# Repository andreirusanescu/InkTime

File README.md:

# InkTime

An affordable, open-source smartwatch powered by the nRF52840 with an e-paper display, designed for low power consumption and BLE connectivity.

## Hardware Diagram

The InkTime smartwatch is built around the Nordic nRF52840 microcontroller and features the following subsystems:

```
                                    ┌───────────────────┐
                                    │    USB-C (J4)     │
                                    └──┬─────────────┬──┘
                                 VBUS  │             │ D+, D-
                                       │      ┌──────▼────────┐
                          ┌────────────┤      │  USBLC6 (D3)  │
                          │            │      │ ESD Protection│
                          │            │      └──────┬────────┘
                          │            │             │ D+, D- (protected)
                   ┌──────▼────────┐   │      ┌──────▼─────────────────────────┐
                   │  BQ25180 (IC3)│   │      │                                │
                   │  LiPo Charger │   │      │        nRF52840 (NRF52840_QF)  │
                   │  (I2C config) │   │      │        ARM Cortex-M4F @ 64MHz  │
                   └──────┬────────┘   │      │        BLE 5.0                 │
                          │            │      │                                │
                    VBAT  │     VBUS   │      │  ┌─────────────────────────┐   │
          ┌───────────────┤◄───────────┘      │  │ Interfaces:             │   │
          │               │                   │  │  SPI  → E-Paper Display │   │
   ┌──────▼────────┐      │                   │  │  I2C  → BMA423, DRV2605 │   │
   │ LiPo Battery  │      │                   │  │         MAX17048,       │   │
   │ LP502030      │      │                   │  │         BQ25180, RT6160 │   │
   │ 3.7V / 250mAh │      │                   │  │  USB  → USB-C (J4)      │   │
   └──────┬────────┘      │                   │  │  GPIO → Buttons, EPD    │   │
          │ VBAT          │                   │  │         ctrl, Haptic EN │   │
   ┌──────▼────────┐      │                   │  │  SWD  → TC2030 (J1)     │   │
   │ MAX17048 (U1) │──────│── I2C ───────────►│  └─────────────────────────┘   │
   │ Fuel Gauge    │      │                   │                                │
   │ (ALERT → GPIO)│      │                   │◄──── 32MHz Crystal (X1)        │
   └───────────────┘      │                   │◄──── 32.768kHz Crystal (X2)    │
                          │                   │◄──── 2.4GHz Antenna (ANT1)     │
                   ┌──────▼────────┐          │      via matching network      │
                   │  RT6160 (IC1) │          │      (L1, C3, C4, C9)          │
                   │  DC/DC        │          │                                │
                   │  Buck-Boost   │ VREG/3V3 │                                │
                   │  (I2C config) ├─────────►│                                │
                   └───────────────┘          └──┬──────┬──────┬───────────┬───┘
                                                 │      │      │           │
                              SPI (MOSI,SCK,CS)  │      │      │           │ GPIO
                              + GPIO ctrl        │      │ I2C  │ I2C       │ (SW_UP P0.26)
                                                 │      │      │           │ (SW_DN P0.27)
                  ┌──────────────────────┐       │      │      │       ┌───▼──────────────────┐
                  │  1.54" E-Paper (J2)  │◄──────┘      │      │       │  3×  │        Buttons│
                  │  200×200px SPI       │              │      │       │  EVP-AKE31A          │
                  │                      │              │      │       │  (SW_ENT P1.00)      │
                  │  EPD Boost Circuit:  │              │      │       └──────────────────────┘
                  │  Q1 (DMG2305UX)      │              │      │
                  │  Q3 (SI1308EDL)      │       ┌──────▼──┐   │
                  │  D2,D4,D5 (MBR0530)  │       │ BMA423  │   │
                  │  L5 (68µH)           │       │  (IC2)  │   │
                  │  → PREVGH, PREVGL    │       │  IMU    │   │
                  └──────────────────────┘       └─────────┘   │
                                                        ┌──────▼──────┐
                           ┌──────────────┐             │  DRV2605    │
                           │  TC2030 (J1) │             │   (IC4)     │
                           │  SWD Debug   │             │  Haptic     │
                           │  (SWDIO,     │             │  Driver     │
                           │   SWDCLK,    │             │  + Motor    │
                           │   SWO, RST)  │             │  (FIT0774)  │
                           └──────────────┘             └─────────────┘
```

## Bill of Materials (BOM)

| Component | Value/Part Number | Package | Qty | Description | Datasheet |
|-----------|-------------------|---------|-----|-------------|-----------|
| NRF52840_QF | nRF52840 | AQFN-73 | 1 | MCU with BLE 5.0 | [Datasheet](https://infocenter.nordicsemi.com/pdf/nRF52840_PS_v1.1.pdf) |
| IC1 | RT6160AWSC | WL-CSP-15 | 1 | DC/DC Buck-Boost Converter | [Datasheet](https://www.richtek.com/assets/product_file/RT6160A/DS6160A-05.pdf) |
| IC2 | BMA423 | LGA-12 | 1 | Triaxial Accelerometer (IMU) | [Datasheet](https://www.bosch-sensortec.com/products/motion-sensors/accelerometers/bma423/) |
| IC3 | BQ25180YBGR | DSBGA-8 | 1 | LiPo Charger | [Datasheet](https://www.ti.com/lit/ds/symlink/bq25180.pdf) |
| IC4 | DRV2605YZFR | WCSP-9 | 1 | Haptic Driver | [Datasheet](https://www.ti.com/lit/ds/symlink/drv2605.pdf) |
| U1 | MAX17048G+T10 | TDFN-8 | 1 | Fuel Gauge | [Datasheet](https://www.analog.com/media/en/technical-documentation/data-sheets/max17048-max17049.pdf) |
| D3 | USBLC6-2SC6Y | SOT-23-6 | 1 | ESD Protection | [Datasheet](https://www.st.com/resource/en/datasheet/usblc6-2.pdf) |
| ANT1 | 2450AT18B100E | SMD | 1 | 2.4GHz Chip Antenna | [Datasheet](https://www.johansontechnology.com/datasheets/antennas/2450AT18B100.pdf) |
| X1 | 32MHz Crystal | SMD 2016 | 1 | Main Clock | - |
| X2 | 32.768kHz Crystal | SMD 3215 | 1 | RTC Clock | - |
| J1 | TC2030-IDC | Tag-Connect | 1 | SWD Debug Header | [Datasheet](https://www.tag-connect.com/product/tc2030-idc) |
| J2 | 503480-2400 | FPC-24 | 1 | E-Paper FPC Connector | [Datasheet](https://www.molex.com/en-us/part-list/503480-2400) |
| J4 | KH-TYPE-C-16P | SMD | 1 | USB-C Connector | - |
| Q1 | DMG2305UX-7 | SOT-23 | 1 | P-Ch MOSFET (EPD drive) | [Datasheet](https://www.diodes.com/assets/Datasheets/DMG2305UX.pdf) |
| Q3 | SI1308EDL-T1-GE3 | SC-70 | 1 | N-Ch MOSFET (EPD drive) | [Datasheet](https://www.vishay.com/docs/68986/si1308edl.pdf) |
| D2, D4, D5 | MBR0530 | SOD-123 | 3 | Schottky Diode (EPD drive) | - |
| L1 | 3.9nH | SMD 2012 | 1 | RF Matching Network | - |
| L2 | 10µH | SMD 2012 | 1 | nRF Power Inductor | - |
| L3 | 15nH | SMD 2012 | 1 | RF Filter | - |
| L5 | 68µH | SMD 2012 | 1 | EPD Boost Inductor | - |
| L7 | FTC252012SR47MBCA | SMD 2012 | 1 | DC/DC Power Inductor (0.47µH) | [JLCPCB](https://jlcpcb.com/partdetail/6763488-FTC252012SR47MBCA/C5832368) |
| SW_UP, SW_DN, SW_ENT | EVP-AKE31A | SMD | 3 | Tactile Buttons | - |
| SJ1 | Solder Jumper | SMD | 1 | Configuration Jumper | - |
| R1, R2, R5 | 0Ω | 0201 | 3 | Zero-ohm Resistors | - |
| R3, R4 | 3.3kΩ | 0201 | 2 | I2C Pull-up Resistors | - |
| R6, R2_EP_DR, R_PWR_EPD | 10kΩ | 0201 | 3 | Pull-up/Pull-down | - |
| R7, R8, R9 | 10kΩ | 0201 | 3 | Button Pull-down Resistors | - |
| R1_USB, R2_USB | 5.1kΩ | 0201 | 2 | USB-C CC Pull-down | - |
| R_TYPE_SEL | 2.2Ω | 0201 | 1 | EPD Type Select | - |
| R1_EP_DR | 0.47Ω | 0201 | 1 | EPD Current Sense | - |
| C1, C2, C17, C18 | 12pF | 0201 | 4 | Crystal Load Capacitors | - |
| C3, C4 | 1pF | 0201 | 2 | RF Matching | - |
| C9 | 820pF | 0201 | 1 | RF Matching | - |
| C5, C7, C8, C12, C19 | 100nF | 0201 | 5 | Decoupling Capacitors | - |
| C11 | 100pF | 0201 | 1 | Decoupling (DEC5) | - |
| C16 | 47nF | 0201 | 1 | Decoupling | - |
| C15 | 1.0µF | 0402 | 1 | Decoupling | - |
| C6, C14, C20, C21, C43, C2-EP-DR | 4.7µF | 0402 | 6 | Bulk Capacitors | - |
| C24, C39, C1-EP-DR | 10µF | 0402 | 3 | Input/Output Caps | - |
| C25, C33 | 22µF | 0402 | 2 | DC/DC Output Caps | - |
| C23, C27, C34, C42, EPD_C5 | 0.1µF | 0201 | 5 | Decoupling | - |
| C29-C32, C37, C38, EPD_C1-C12 | 1µF | 0402 | 15 | Filter/Bypass Caps | - |
| C10, C13, C22 | N.C. | 0201 | 3 | Do Not Populate | - |
| Test Pads | - | SMD | 14 | TP_GND, TP_3V3, TP_VBAT, etc. | - |

## Hardware Description

### Microcontroller — nRF52840 (NRF52840_QF)
The nRF52840 is the core of the InkTime, providing Bluetooth Low Energy 5.0 connectivity, ARM Cortex-M4F processing at 64MHz, and extensive GPIO. It communicates with peripherals via I2C and SPI buses and is powered by 3.3V from the RT6160 DC/DC converter.

Two crystals provide clock sources: a 32MHz crystal (X1) connected to XC1/XC2 with 12pF load capacitors (C1, C2), and a 32.768kHz crystal (X2) connected to P0.00/XL1 and P0.01/XL2 with 12pF load capacitors (C17, C18).

The RF section uses a 2450AT18B100E chip antenna connected through an impedance matching network (L1=3.9nH, C3=1pF, C4=1pF, C9=820pF) to the ANT pin. The antenna is placed at the edge of the PCB with a copper keepout zone on all layers underneath.

Decoupling capacitors placed close to corresponding power pins: C5 (100nF) on DEC1, C8 (100nF) on DEC3, C7 (100nF) on DEC4_6, C11 (100pF) on DEC5, C15 (1.0µF). Capacitors C10, C13, C22 are N.C. (Do Not Populate) per Nordic's reference design.

### Power Management

**LiPo Charger — BQ25180 (IC3):** Manages battery charging from USB-C (VBUS). Single-cell LiPo battery connected directly to test pads (TP_VBAT, TP_BAT_GND). I2C configurable. Interrupt output (PMIC_INT) to nRF52840. Bypass capacitors C37 (1µF), C39 (10µF). Pull-up R6 (10kΩ) on TS/MR.

**DC/DC Converter — RT6160 (IC1):** Buck-boost converter, VBAT (3.0–4.2V) to VREG/3V3. I2C voltage selection via VSEL pin. Power inductor L7 (0.47µH). Input cap C23 (0.1µF), output caps C24 (10µF), C25 (22µF), C33 (22µF). I2C pull-ups R3, R4 (3.3kΩ).

**Fuel Gauge — MAX17048 (U1):** Battery monitoring via I2C. CELL pin to VBAT, ALERT output to nRF52840. Bypass cap C38 (1µF).

### Display — 1.54" E-Paper (via J2, 503480-2400)
SPI interface (MOSI, SCK, EPD_CS). Drive circuit with Q3 (SI1308EDL), Q1 (DMG2305UX), diodes D2/D4/D5 (MBR0530), inductor L5 (68µH), and capacitors EPD_C1–C12 for high-voltage generation (PREVGH, PREVGL). Control: EPD_RST, EPD_BUSY, EPD_DC.

### IMU — BMA423 (IC2)
Triaxial accelerometer via I2C (SDA, SCL). Two interrupt outputs (IMU_INT1, IMU_INT2) for motion/step/gesture detection. Decoupling C19 (100nF). Zero-ohm resistors R1, R2, R5 for pin configuration.

### Haptic Driver — DRV2605 (IC4)
I2C haptic driver for vibration motor (FIT0774). Enable via HAPTIC_EN GPIO. Decoupling C32 (1µF), C34 (0.1µF).

### USB-C and ESD Protection
KH-TYPE-C-16P connector (J4). USBLC6-2SC6Y (D3) ESD protection. CC pull-downs R1_USB, R2_USB (5.1kΩ). Bypass caps C42 (0.1µF), C43 (4.7µF).

### SWD Debug — TC2030-IDC (J1)
Tag-Connect pogo-pin interface: SWDIO, SWDCLK, SWO, RESET, 3.3V, GND. No permanent connector needed.

## nRF52840 Pin Assignment

| Pin | Signal | Function | Interface |
|-----|--------|----------|-----------|
| P0.00/XL1 | XL1 | 32.768kHz Crystal | Clock |
| P0.01/XL2 | XL2 | 32.768kHz Crystal | Clock |
| P0.04/AIN2 | IMU_INT1 | BMA423 Interrupt 1 | GPIO |
| P0.05/AIN3 | IMU_INT2 | BMA423 Interrupt 2 | GPIO |
| P0.06 | EPD_CS | E-Paper Chip Select | SPI |
| P0.07 | EPD_DC | E-Paper Data/Command | GPIO |
| P0.08 | EPD_RST | E-Paper Reset | GPIO |
| P0.09/NFC1 | PMIC_INT | BQ25180 Interrupt | GPIO |
| P0.11 | SCK | SPI Clock (E-Paper) | SPI |
| P0.12 | MOSI | SPI Data (E-Paper) | SPI |
| P0.13 | EPD_BUSY | E-Paper Busy | GPIO |
| P0.14 | SCL | I2C Clock | I2C |
| P0.15 | SDA | I2C Data | I2C |
| P0.18/RESET | RESET | System Reset | Reset |
| P0.19 | HAPTIC_EN | DRV2605 Enable | GPIO |
| P0.26 | SW_UP | Button Up | GPIO |
| P0.27 | SW_DN | Button Down | GPIO |
| P1.00 | SW_ENT | Button Enter | GPIO |
| P1.01 | ALERT | MAX17048 Alert | GPIO |
| P1.09 | SWO | Debug Trace Output | Debug |
| XC1/XC2 | Crystal | 32MHz Oscillator | Clock |
| ANT | RF | Antenna via matching | RF |
| VBUS | USB_VBUS | USB Power (5V) | Power |
| D+/D- | USB Data | USB Data Lines | USB |
| SWDIO | Debug | SWD Data | Debug |
| SWDCLK | Debug | SWD Clock | Debug |

**I2C Bus** shared by: BMA423 (IC2), BQ25180 (IC3), RT6160 (IC1), DRV2605 (IC4), MAX17048 (U1). Pull-ups R3, R4 (3.3kΩ) to 3V3.

## PCB Design Details

### Board Specifications
- **Dimensions:** 46mm × 35mm, rounded corners
- **Layers:** 4 (Top, Route2, Route63, Bottom)
- **Thickness:** 1.0mm
- **Trace widths:** 0.15mm (signals), 0.3mm (power)
- **Components:** All on TOP layer

### Layer Stack
| Layer | Name | Function |
|-------|------|----------|
| 1 | ct Top | Signals + GND polygon |
| 2 | c2 Route2 | Dedicated GND plane |
| 63 | c63 Route63 | Signal routing |
| 64 | cb Bottom | Signals + GND polygon |

### Design Decisions and Accepted Errors
- **Copper Width errors (accepted)**: Power nets (3V3, VREG, VBAT, VBUS, etc.) require 0.3mm trace width per design rules. However, in some dense areas of the board - particularly around small IC packages and tight pad spacing - there is not enough physical space to maintain 0.3mm width for the entire trace length. The resulting DRC errors were accepted.
- **Copper Clearance errors (accepted)**: In highly congested areas, especially around the nRF52840 BGA and the dense passive component clusters, some traces and pads come closer together than the 0.15mm clearance rule allows. These violations occur where component placement leaves no alternative routing path and were accepted after manual verification that no actual shorts exist.
- **Overlapping / Polygon Clearance errors (accepted)**: Some GND polygons on different layers generate clearance warnings where they overlap with same-rank polygons. These are non-functional warnings — the polygons are all on the same net (GND) and do not cause electrical issues.
- **Board Outline Clearance errors (accepted)**: The three tactile buttons (SW_UP, SW_DN, SW_ENT) and the USB-C connector (J4) intentionally extend beyond the PCB edge for mechanical alignment with the enclosure cutouts. This is by design and explicitly permitted in the project specification.
- **N.C. capacitors (C10, C13, C22):** Footprints present but not populated per Nordic reference.
- **Silkscreen:** Labels on IC's, connectors, test pads, capacitors etc.
- **Via stitching**: GND vias are distributed across the board between all ground planes, with higher concentration around the nRF52840 and RF antenna area, to ensure low-impedance ground return paths at 2.4GHz.

## Mechanical

| Component | Dimensions | Notes |
|-----------|-----------|-------|
| Battery (AKYGA LP502030) | 32.5 × 21 × 5.5mm | 3.7V/250mAh, soldered to test pads |
| Display (1.54" e-Paper V2) | 37.32 × 31.80 × 1.05mm | 200×200px, SPI, ultra-low power |
| Vibration Motor (FIT0774) | Ø10 × 2.7mm | 1.5–4.2VDC, 50mA |
| Enclosure | Custom | 3D-printed, cutouts for USB/buttons |

## Repository Structure

```
├── Hardware/
│   ├── InkTime_Schematic.sch
│   └── InkTime_Board.brd
├── Manufacturing/
│   ├── gerbers.zip
│   ├── InkTime_BOM.bom
│   └── InkTime_PnP.cpl
├── Mechanical/
│   ├── InkTime_step.step
│   └── InkTime_complete.f3z
├── Images/
│   ├── 2D_PCB/          (PCB layer views: Top, Bottom, C2, C63)
│   ├── 3D_PCB/          (3D renders of the PCB)
│   ├── InkTime/         (Watch assembly renders)
│   └── Schematic/       (Schematic screenshots)
├── LICENSE
└── README.md
```

## Images

### Watch Assembly

| Top View | Side View (Buttons) | USB-C Port |
|----------|---------------------|------------|
|  |  |  |

### Exploded View

| Side View (Exploded) | Front View (Exploded) |
|----------------------|-----------------------|
|  |  |

### 3D Component Models

| Display (Top) | Display (Side — Rounded Edges) | Display (Edges) |
|---------------|-------------------------------|-----------------|
|  |  |  |

| Battery (LP502030) | Shaker Motor (FIT0774) |
|--------------------|------------------------|
|  |  |

### PCB Renders

| 3D Top View | 3D Side View |
|-------------|--------------|
|  |  |

### PCB Layers

| Top Layer | Inner Layer 2 (GND) | Inner Layer 63 (Signal) | Bottom Layer |
|-----------|---------------------|------------------------|--------------|
|  |  |  |  |

### Schematic

| Page 1 | Page 2 |
|--------|--------|
|  |  |

## License

This project is open source hardware, licensed under the [Apache License 2.0](LICENSE).

Distributed as-is; no warranty is given.

---

*Designed as part of the InkTime project — TSC course, Politehnica Bucharest, 2026.*

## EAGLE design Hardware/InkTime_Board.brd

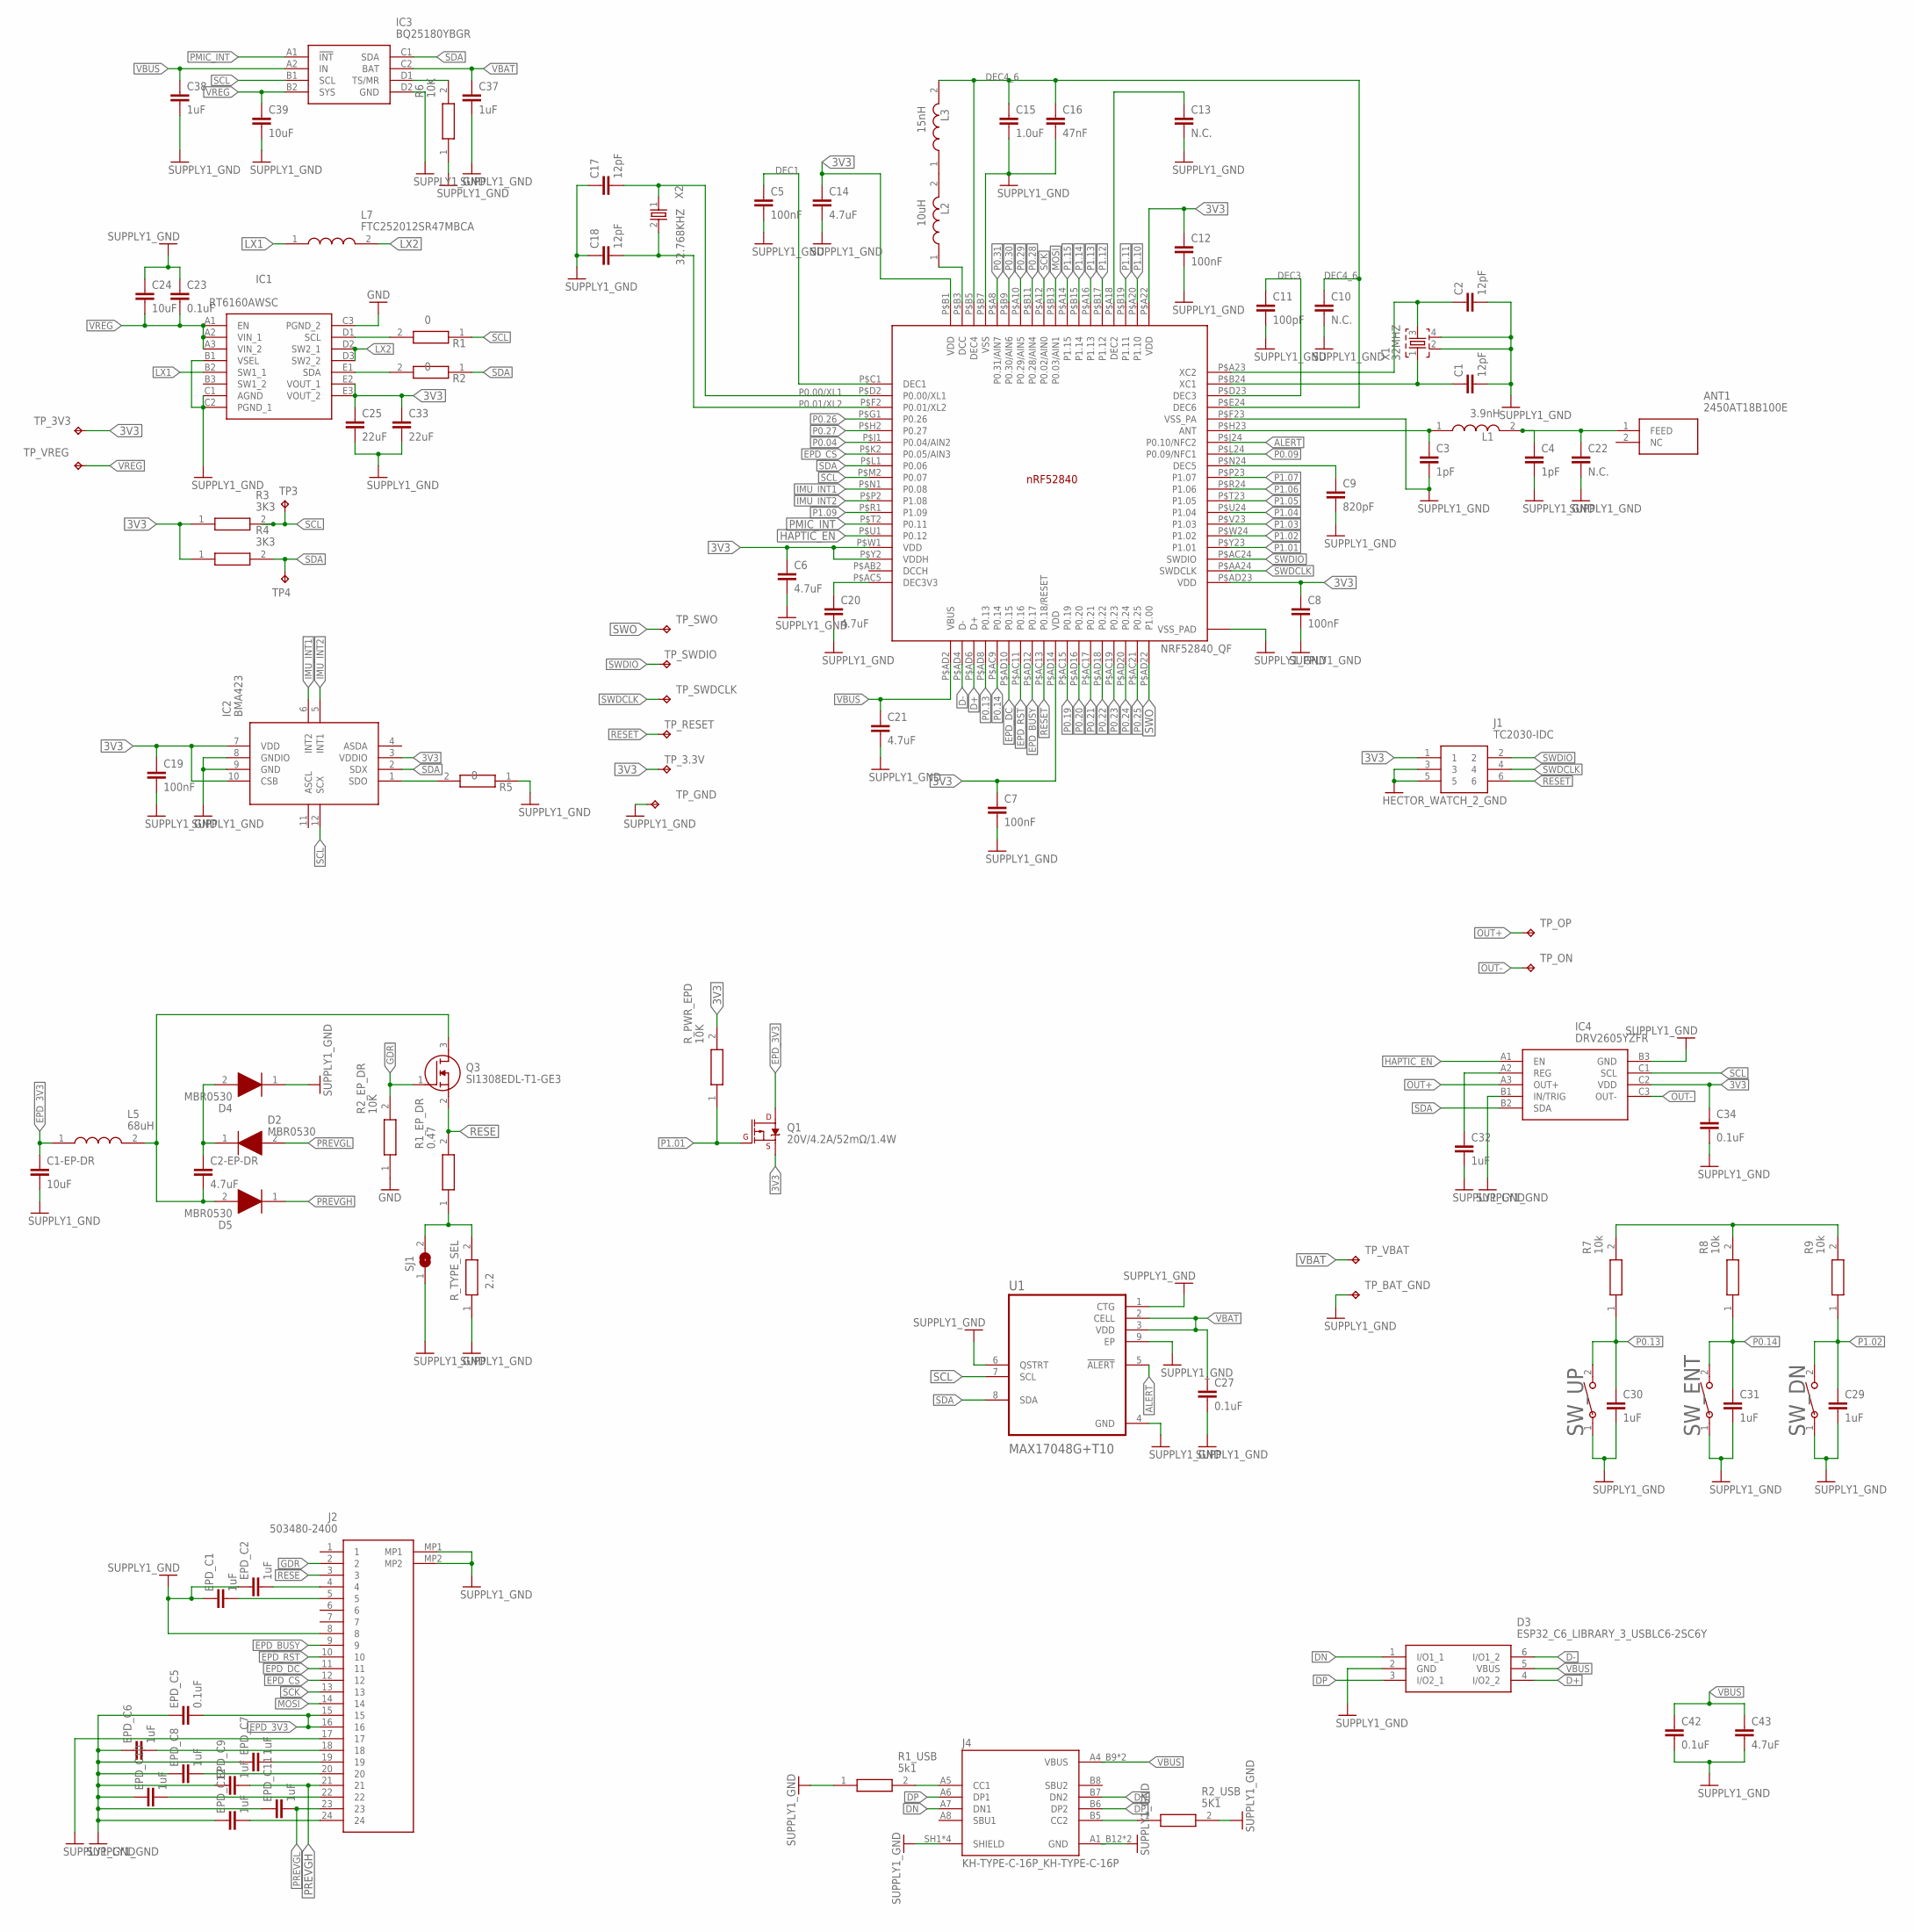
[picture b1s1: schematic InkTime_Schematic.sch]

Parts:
ANT1: 2450AT18B100E; 2450AT18B100E_ANTC3216X140N
C1, C2, C17, C18: 12pF; NORDIC_NRF_3_RESC0201_L
C1-EP-DR, C24, C39: 10uF; NORDIC_NRF_3_RESC0402_L
C2-EP-DR, C6, C14, C20, C21, C43: 4.7uF; NORDIC_NRF_3_RESC0402_L
C3, C4: 1pF; NORDIC_NRF_3_RESC0201_L
C5, C7, C8, C12, C19: 100nF; NORDIC_NRF_3_RESC0201_L
C9: 820pF; NORDIC_NRF_3_RESC0201_L
C10, C13, C22: N.C.; NORDIC_NRF_3_RESC0201_L
C11: 100pF; NORDIC_NRF_3_RESC0201_L
C15: 1.0uF; NORDIC_NRF_3_RESC0402_L
C16: 47nF; NORDIC_NRF_3_RESC0201_L
C23, C27, C34, C42: 0.1uF; NORDIC_NRF_3_RESC0201_L
C25, C33: 22uF; NORDIC_NRF_3_RESC0402_L
C29, C30, C31, C32, C37, C38: 1uF; NORDIC_NRF_3_RESC0402_L
D2, D4, D5: MBR0530; ESP32_C6_LIBRARY_5_SOD3716X135N
D3: ESP32_C6_LIBRARY_3_USBLC6-2SC6Y; ESP32_C6_LIBRARY_3_SOT95P280X145-6N
EPD_C1, EPD_C2, EPD_C6, EPD_C7, EPD_C8, EPD_C9, EPD_C10, EPD_C11, EPD_C12: 1uF; NORDIC_NRF_3_RESC0402_L
EPD_C5: 0.1uF; NORDIC_NRF_3_RESC0201_L
IC1: RT6160AWSC; RT6160AWSC_BGA15C40P3X5_140X230X60
IC2: BMA423; BMA423_BMA423
IC3: BQ25180YBGR; BQ25180YBGR_BGA8C40P2X4_100X155X50
IC4: DRV2605YZFR; DRV2605YZFR_BGA9C50P3X3_144X144X62
J1: TC2030-IDC; TC2030-IDC_TC2030IDC
J2: 503480-2400; 503480-2400_5034802400
J4: KH-TYPE-C-16P_KH-TYPE-C-16P; KH-TYPE-C-16P_KINGHELM_KH-TYPE-C-16P
L1: 3.9nH; MLP2016SR47MT0S1_INDC2016X100N
L2: 10uH; MLP2016SR47MT0S1_INDC2016X100N
L3: 15nH; MLP2016SR47MT0S1_INDC2016X100N
L5: 68uH; MLP2016SR47MT0S1_INDC2016X100N
L7: FTC252012SR47MBCA; MLP2016SR47MT0S1_INDC2016X100N
NRF52840_QF: NRF52840_QF; NORDIC_NRF_4_AQFN50P700X700X85_HS-74N
Q1: 20V/4.2A/52mΩ/1.4W; ESP32_C6_LIBRARY_4_ESP32_C6_LIBRARY_4_ESP32_C6_LIBRARY_4_ES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
Q3: SI1308EDL-T1-GE3; ESP32_C6_LIBRARY_6_SOT65P210X110-3N
R1, R2, R5: 0; CPF0201D7K68C1_0201
R1_EP_DR: 0.47; CPF0201D7K68C1_0201
R1_USB: 5k1; CPF0201D7K68C1_0201
R2_EP_DR, R6: 10K; CPF0201D7K68C1_0201
R2_USB: 5K1; CPF0201D7K68C1_0201
R3, R4: 3K3; CPF0201D7K68C1_0201
R7, R8, R9: 10k; CPF0201D7K68C1_0201
R_PWR_EPD: 10K; CPF0201D7K68C1_0201
R_TYPE_SEL: 2.2; CPF0201D7K68C1_0201
SJ1: ESP32_C6_LIBRARY_7_JUMPER_SJ
SW_DN: EVP-AKE31A_PAN; 2025-10-22_07-23-44_LIBRARY_SW_EVP-AKE31A_PAN
SW_ENT: EVP-AKE31A_PAN; 2025-10-22_07-23-44_LIBRARY_SW_EVP-AKE31A_PAN
SW_UP: EVP-AKE31A_PAN; 2025-10-22_07-23-44_LIBRARY_SW_EVP-AKE31A_PAN
TP3, TP4: HECTOR_WATCH_1_TPTP20R; HECTOR_WATCH_1_TP20R
TP_3.3V, TP_3V3: HECTOR_WATCH_1_TPTP20R; HECTOR_WATCH_1_TP20R
TP_BAT_GND: HECTOR_WATCH_1_TPTP20R; HECTOR_WATCH_1_TP20R
TP_GND: HECTOR_WATCH_1_TPTP20R; HECTOR_WATCH_1_TP20R
TP_ON: HECTOR_WATCH_1_TPTP20R; HECTOR_WATCH_1_TP20R
TP_OP: HECTOR_WATCH_1_TPTP20R; HECTOR_WATCH_1_TP20R
TP_RESET: HECTOR_WATCH_1_TPTP20R; HECTOR_WATCH_1_TP20R
TP_SWDCLK: HECTOR_WATCH_1_TPTP20R; HECTOR_WATCH_1_TP20R
TP_SWDIO: HECTOR_WATCH_1_TPTP20R; HECTOR_WATCH_1_TP20R
TP_SWO: HECTOR_WATCH_1_TPTP20R; HECTOR_WATCH_1_TP20R
TP_VBAT: HECTOR_WATCH_1_TPTP20R; HECTOR_WATCH_1_TP20R
TP_VREG: HECTOR_WATCH_1_TPTP20R; HECTOR_WATCH_1_TP20R
U1: MAX17048G+T10; ESP32_C6_LIBRARY_SON50P200X200X80-9N
X1: 32MHZ; NORDIC_NRF_BT-XTAL_2016_N
X2: 32.768KHZ; NORDIC_NRF_1_XTAL_3215_N

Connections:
3V3: C7.1, C8.1, C12.1, C14.1, C19.1, C34.1, IC2.3 (VDDIO), IC2.7 (VDD), IC2.10 (CSB), IC4.C2 (VDD), J1.1, NRF52840_QF.P$A22 (VDD), NRF52840_QF.P$AD14 (VDD), NRF52840_QF.P$AD23 (VDD), NRF52840_QF.P$B1 (VDD), Q1.2 (S), R_PWR_EPD.2, TP_3.3V.TP, TP_3V3.TP
ALERT: NRF52840_QF.P$J24 (P0.10/NFC2), U1.5 (!ALERT)
D+: D3.4 (I/O2_2), NRF52840_QF.P$AD6 (D+)
D-: D3.6 (I/O1_2), NRF52840_QF.P$AD4 (D-)
DEC1: C5.1, NRF52840_QF.P$C1 (DEC1)
DEC3: C11.1, NRF52840_QF.P$D23 (DEC3)
DEC4_6: C10.1, C15.1, C16.1, L3.2, NRF52840_QF.P$B5 (DEC4), NRF52840_QF.P$E24 (DEC6)
DN: D3.1 (I/O1_1), J4.A7 (DN1), J4.B7 (DN2)
DP: D3.3 (I/O2_1), J4.A6 (DP1), J4.B6 (DP2)
EPD_3V3: C1-EP-DR.1, EPD_C5.2, J2.15, J2.16, L5.1, Q1.3 (D)
EPD_BUSY: J2.9, NRF52840_QF.P$AD12 (P0.17)
EPD_CS: J2.12, NRF52840_QF.P$K2 (P0.05/AIN3)
EPD_DC: J2.11, NRF52840_QF.P$AD10 (P0.15)
EPD_RST: J2.10, NRF52840_QF.P$AC11 (P0.16)
GDR: J2.2, Q3.1 (G), R2_EP_DR.2
GND: C1.2, C1-EP-DR.2, C2.2, C3.2, C4.2, C5.2, C6.2, C7.2, C8.2, C9.2, C10.2, C11.2, C12.2, C13.2, C14.2, C15.2, C16.2, C17.1, C18.1, C19.2, C20.2, C21.2, C22.2, C23.1, C24.1, C25.2, C27.2, C29.2, C30.2, C31.2, C32.2, C33.2, C34.2, C37.2, C38.2, C39.2, C42.2, C43.2, D3.2 (GND), D4.1 (K), EPD_C1.1, EPD_C2.1, EPD_C5.1, EPD_C6.1, EPD_C7.1, EPD_C8.1, EPD_C9.1, EPD_C10.1, EPD_C11.1, EPD_C12.1, IC1.B1 (VSEL), IC1.C1 (AGND), IC1.C2 (PGND_1), IC1.C3 (PGND_2), IC2.8 (GNDIO), IC2.9 (GND), IC3.D2 (GND), IC4.B1 (IN/TRIG), IC4.B3 (GND), J1.3, J1.5, J2.8, J2.17, J2.MP1, J2.MP2, J4.A1_B12 (GND), J4.A12_B1 (GND), J4.SH1 (SHIELD), J4.SH2 (SHIELD), J4.SH3 (SHIELD), J4.SH4 (SHIELD), NRF52840_QF.P$74 (VSS_PAD), NRF52840_QF.P$75 (VSS_PAD), NRF52840_QF.P$76 (VSS_PAD), NRF52840_QF.P$77 (VSS_PAD), NRF52840_QF.P$78 (VSS_PAD), NRF52840_QF.P$79 (VSS_PAD), NRF52840_QF.P$80 (VSS_PAD), NRF52840_QF.P$81 (VSS_PAD), NRF52840_QF.P$82 (VSS_PAD), NRF52840_QF.P$83 (VSS_PAD), NRF52840_QF.P$84 (VSS_PAD), NRF52840_QF.P$85 (VSS_PAD), NRF52840_QF.P$86 (VSS_PAD), NRF52840_QF.P$87 (VSS_PAD), NRF52840_QF.P$88 (VSS_PAD), NRF52840_QF.P$89 (VSS_PAD), NRF52840_QF.P$90 (VSS_PAD), NRF52840_QF.P$B7 (VSS), NRF52840_QF.P$F23 (VSS_PA), R1_USB.1, R2_EP_DR.1, R2_USB.2, R5.1, R6.1, R_TYPE_SEL.1, SJ1.1, SW_DN.1, SW_ENT.1, SW_UP.1, TP_BAT_GND.TP, TP_GND.TP, U1.1 (CTG), U1.4 (GND), U1.6 (QSTRT), U1.9 (EP), X1.2, X1.4
HAPTIC_EN: IC4.A1 (EN), NRF52840_QF.P$U1 (P0.12)
IMU_INT1: IC2.6 (INT2), NRF52840_QF.P$N1 (P0.08)
IMU_INT2: IC2.5 (INT1), NRF52840_QF.P$P2 (P1.08)
LX1: IC1.B2 (SW1_1), L7.1
LX2: IC1.D2 (SW2_1), IC1.D3 (SW2_2), L7.2
MOSI: J2.14, NRF52840_QF.P$B13 (P0.03/AIN1)
unnamed: C1.1, NRF52840_QF.P$B24 (XC1), X1.1
unnamed: ANT1.1 (FEED), C4.1, C22.1, L1.2
unnamed: C3.1, L1.1, NRF52840_QF.P$H23 (ANT)
unnamed: C2.1, NRF52840_QF.P$A23 (XC2), X1.3
unnamed: C6.1, NRF52840_QF.P$W1 (VDD), NRF52840_QF.P$Y2 (VDDH)
unnamed: C20.1, NRF52840_QF.P$AC5 (DEC3V3)
unnamed: C13.1, NRF52840_QF.P$A18 (DEC2)
unnamed: L2.1, NRF52840_QF.P$B3 (DCC)
unnamed: L2.2, L3.1
unnamed: IC1.D1 (SCL), R1.2
unnamed: IC1.E1 (SDA), R2.2
unnamed: C9.1, NRF52840_QF.P$N24 (DEC5)
unnamed: C25.1, C33.1, IC1.E2 (VOUT_1), IC1.E3 (VOUT_2)
unnamed: R3.1, R4.1
unnamed: C2-EP-DR.1, D2.1 (K), D4.2 (A)
unnamed: IC2.1 (SDO), R5.2
unnamed: C2-EP-DR.2, D5.2 (A), L5.2, Q3.3 (D)
unnamed: IC3.D1 (TS/MR), R6.2
unnamed: R1_EP_DR.1, R_TYPE_SEL.2, SJ1.2
unnamed: C32.1, IC4.A2 (REG)
unnamed: R7.2, R8.2, R9.2
unnamed: J4.A5 (CC1), R1_USB.2
unnamed: EPD_C12.2, J2.24
unnamed: EPD_C2.2, J2.4
unnamed: EPD_C1.2, J2.5
unnamed: J4.B5 (CC2), R2_USB.1
unnamed: EPD_C6.2, J2.18
unnamed: EPD_C7.2, J2.19
unnamed: EPD_C8.2, J2.20
unnamed: EPD_C10.2, J2.22
OUT+: IC4.A3 (OUT+), TP_OP.TP
OUT-: IC4.C3 (OUT-), TP_ON.TP
P0.00/XL1: C17.2, NRF52840_QF.P$D2 (P0.00/XL1), X2.1
P0.01/XL2: C18.2, NRF52840_QF.P$F2 (P0.01/XL2), X2.2
P0.04: NRF52840_QF.P$J1 (P0.04/AIN2)
P0.09: NRF52840_QF.P$L24 (P0.09/NFC1)
P0.13: C30.1, NRF52840_QF.P$AD8 (P0.13), R7.1, SW_UP.2
P0.14: C31.1, NRF52840_QF.P$AC9 (P0.14), R8.1, SW_ENT.2
P0.19: NRF52840_QF.P$AC15 (P0.19)
P0.20: NRF52840_QF.P$AD16 (P0.20)
P0.21: NRF52840_QF.P$AC17 (P0.21)
P0.22: NRF52840_QF.P$AD18 (P0.22)
P0.23: NRF52840_QF.P$AC19 (P0.23)
P0.24: NRF52840_QF.P$AD20 (P0.24)
P0.25: NRF52840_QF.P$AC21 (P0.25)
P0.26: NRF52840_QF.P$G1 (P0.26)
P0.27: NRF52840_QF.P$H2 (P0.27)
P0.28: NRF52840_QF.P$B11 (P0.28/AIN4)
P0.29: NRF52840_QF.P$A10 (P0.29/AIN5)
P0.30: NRF52840_QF.P$B9 (P0.30/AIN6)
P0.31: NRF52840_QF.P$A8 (P0.31/AIN7)
P1.01: NRF52840_QF.P$Y23 (P1.01), Q1.1 (G), R_PWR_EPD.1
P1.02: C29.1, NRF52840_QF.P$W24 (P1.02), R9.1, SW_DN.2
P1.03: NRF52840_QF.P$V23 (P1.03)
P1.04: NRF52840_QF.P$U24 (P1.04)
P1.05: NRF52840_QF.P$T23 (P1.05)
P1.06: NRF52840_QF.P$R24 (P1.06)
P1.07: NRF52840_QF.P$P23 (P1.07)
P1.09: NRF52840_QF.P$R1 (P1.09)
P1.10: NRF52840_QF.P$A20 (P1.10)
P1.11: NRF52840_QF.P$B19 (P1.11)
P1.12: NRF52840_QF.P$B17 (P1.12)
P1.13: NRF52840_QF.P$A16 (P1.13)
P1.14: NRF52840_QF.P$B15 (P1.14)
P1.15: NRF52840_QF.P$A14 (P1.15)
PMIC_INT: IC3.A1 (!INT), NRF52840_QF.P$T2 (P0.11)
PREVGH: D5.1 (K), EPD_C9.2, J2.21
PREVGL: D2.2 (A), EPD_C11.2, J2.23
RESE: J2.3, Q3.2 (S), R1_EP_DR.2
RESET: J1.6, NRF52840_QF.P$AC13 (P0.18/RESET), TP_RESET.TP
SCK: J2.13, NRF52840_QF.P$A12 (P0.02/AIN0)
SCL: IC2.12 (SCX), IC3.B1 (SCL), IC4.C1 (SCL), NRF52840_QF.P$M2 (P0.07), R1.1, R3.2, TP3.TP, U1.7 (SCL)
SDA: IC2.2 (SDX), IC3.C1 (SDA), IC4.B2 (SDA), NRF52840_QF.P$L1 (P0.06), R2.1, R4.2, TP4.TP, U1.8 (SDA)
SWDCLK: J1.4, NRF52840_QF.P$AA24 (SWDCLK), TP_SWDCLK.TP
SWDIO: J1.2, NRF52840_QF.P$AC24 (SWDIO), TP_SWDIO.TP
SWO: NRF52840_QF.P$AD22 (P1.00), TP_SWO.TP
VBAT: C27.1, C37.1, IC3.C2 (BAT), TP_VBAT.TP, U1.2 (CELL), U1.3 (VDD)
VBUS: C21.1, C38.1, C42.1, C43.1, D3.5 (VBUS), IC3.A2 (IN), J4.A4_B9 (VBUS), J4.A9_B4 (VBUS), NRF52840_QF.P$AD2 (VBUS)
VREG: C23.2, C24.2, C39.1, IC1.A1 (EN), IC1.A2 (VIN_1), IC1.A3 (VIN_2), IC3.B2 (SYS), TP_VREG.TP

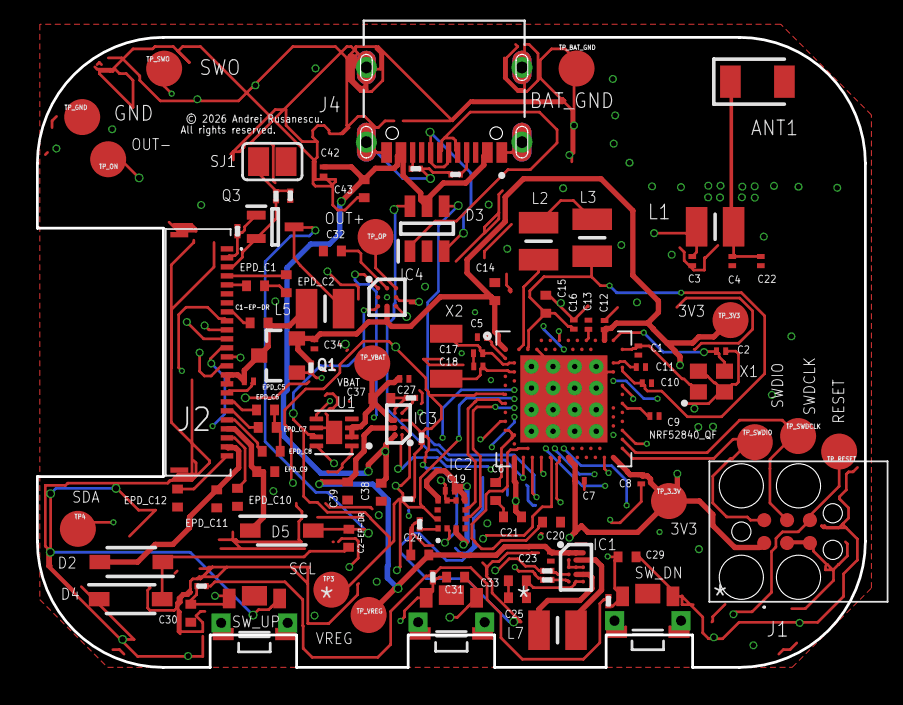
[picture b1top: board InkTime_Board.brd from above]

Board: 4 copper layers, 46.0 x 35.0 mm, 105 parts (0 on the bottom side), 74 nets.

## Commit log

2026-03-26 Added project
2026-03-26 Fixed diagram
2026-03-26 Include Apache License 2.0
    Add Apache License 2.0 to the project
2026-04-03 Rerouted some signals
2026-04-06 Rerouted some other signals. Minor changes to README.md
2026-04-06 Added f3z file
2026-04-07 Rerouted some more. Added BGA
2026-04-09 Improved display rendering. Added more pictures
2026-04-21 Upated routing. Fixes #2, fixes #3, fixes #4, and resolves #5
2026-04-21 Added print-out schematic.pdf. Fixes #1

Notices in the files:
Hardware/InkTime_Board.brd:
© 2026 Andrei Rusanescu.
All rights reserved.
parts and their libraries:
COPYRIGHT: Copyright (C) 2025 Ultra Librarian. All rights reserved.
